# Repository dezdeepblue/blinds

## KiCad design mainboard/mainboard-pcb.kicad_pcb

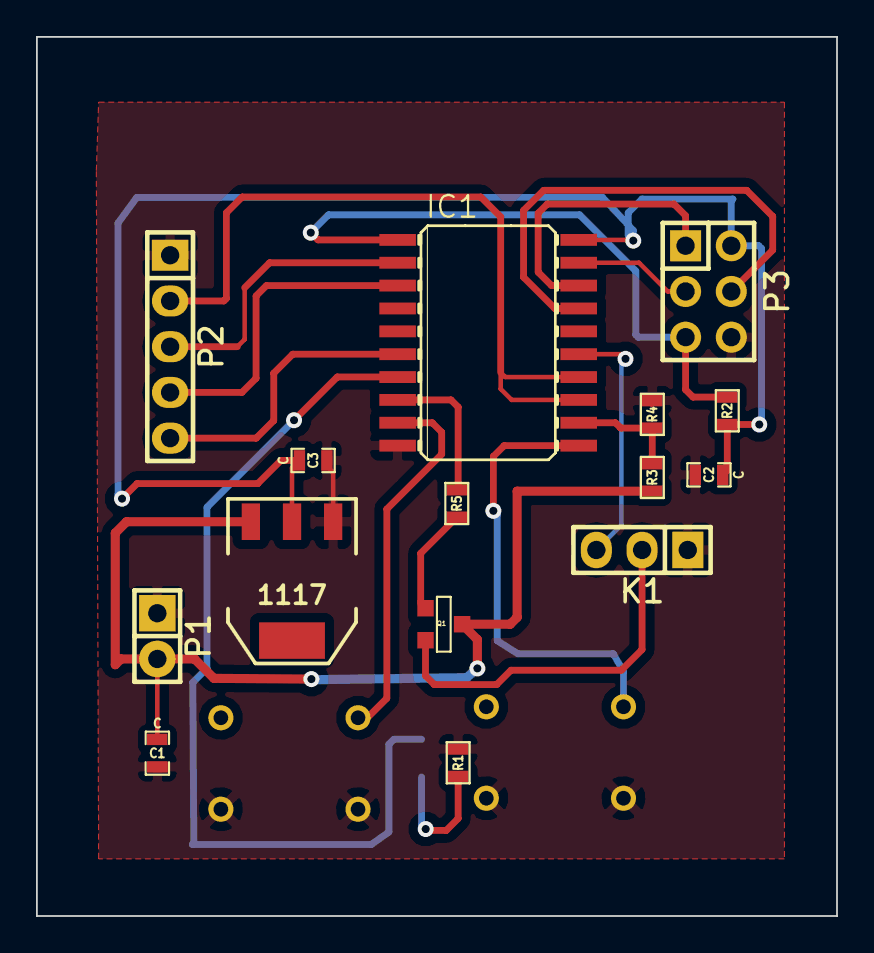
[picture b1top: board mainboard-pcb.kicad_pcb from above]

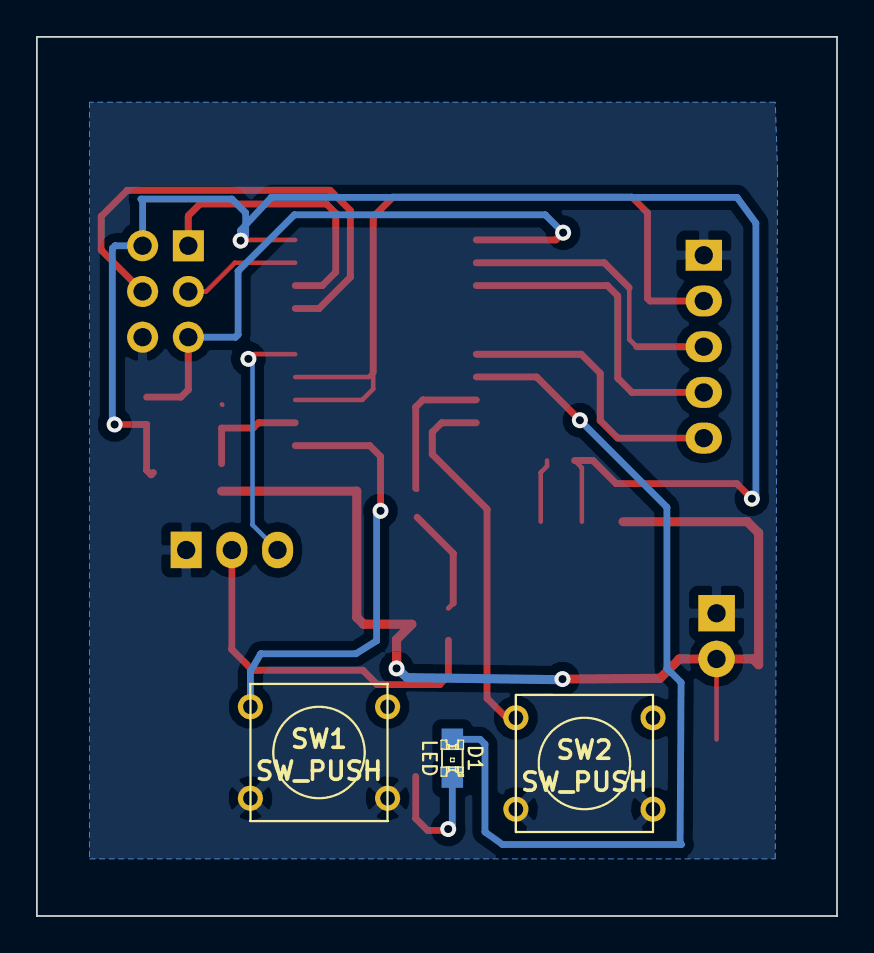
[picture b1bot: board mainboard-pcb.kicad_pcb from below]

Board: 2 copper layers, 44.4 x 48.8 mm, 18 parts (3 on the bottom side), 20 nets.

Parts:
1117: SOT223
C1, C2, C3: C; SM0603_Capa
D1: LED; LED-0805
IC1: ATTINY2313-S; SO20W
K1: CONN_3; Pin_Header_Straight_1x03
P1: CONN_2; Pin_Header_Straight_1x02
P2: CONN_5; Pin_Header_Straight_1x05
P3: CONN_3X2; Pin_Header_Straight_2x03
Q1: Q1; SOT23GDS
R1, R2, R3, R4, R5: R; SM0603
SW1, SW2: SW_PUSH; SW_PUSH_SMALL

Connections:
+BATT: 1117.3, C1.1, P1.2, Q1.D, R3.2
GND: 1117.1, C1.2, C2.2, C3.2, IC1.10, K1.1, P1.1, P2.1, P3.6, R1.2, R4.1, SW1.2, SW2.2
unnamed: 1117.2, C2.1, C3.1, IC1.20, P3.2, R2.1
unnamed: D1.1, IC1.7
unnamed: D1.2, R1.1
unnamed: IC1.1, P3.5, R2.2
unnamed: IC1.2, P2.3
unnamed: IC1.3, P2.4
unnamed: IC1.6, P2.5
unnamed: IC1.8, R5.2
unnamed: IC1.9, SW2.1
unnamed: IC1.11, SW1.1
unnamed: IC1.12, R3.1, R4.2
unnamed: IC1.13, IC1.14, P2.2
unnamed: IC1.15, K1.3
unnamed: IC1.17, P3.4
unnamed: IC1.18, P3.1
unnamed: IC1.19, P3.3
unnamed: K1.2, Q1.S
unnamed: Q1.G, R5.1

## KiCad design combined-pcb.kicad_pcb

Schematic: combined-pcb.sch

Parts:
C1, C2: C; dp_devices-C0.1PTH
J1: CON_HEADER_1X02-PTH; dp_devices-M1X2
J2: CON_HEADER_1X03-PTH; dp_devices-M1X3
Q1, Q2: TRANSISTOR_NPNTO92; SparkFun-TO-92
R1, R2: RESISTOR1206; SparkFun-1206
U1: ARDUINO_MINI
U2: NCP1117ST33T3G
U3: BLUETOOTH-HC05

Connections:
/GND: C1.2, C2.2, J1.1, Q1.1 (E), U1.23 (GND2), U2.1 (GND), U3.13 (GND)
unnamed: C1.1, J1.2, J2.2, U2.3 (VI)
unnamed: C2.1, U1.21 (VCC), U2.2 (VO)
unnamed: J2.1, Q1.3 (C)
unnamed: J2.3, R2.2
unnamed: Q1.2 (B), R1.2
unnamed: R1.1, U1.15 (12)
unnamed: R2.1, U1.13 (10)
unnamed: U1.1 (TX0), U3.2 (UART_RXD)
unnamed: U1.2 (RX1), U3.1 (UART_TXD)
unnamed: U1.8 (5), U3.12 (VCC)

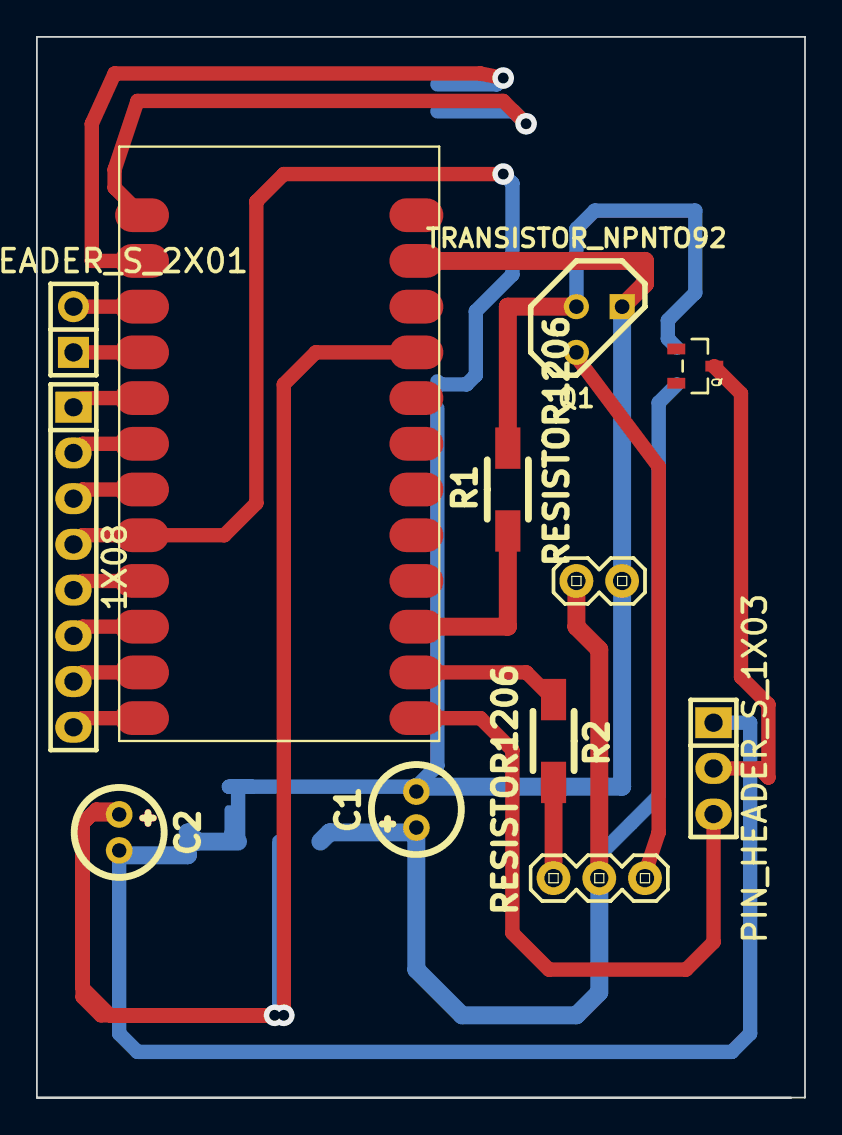
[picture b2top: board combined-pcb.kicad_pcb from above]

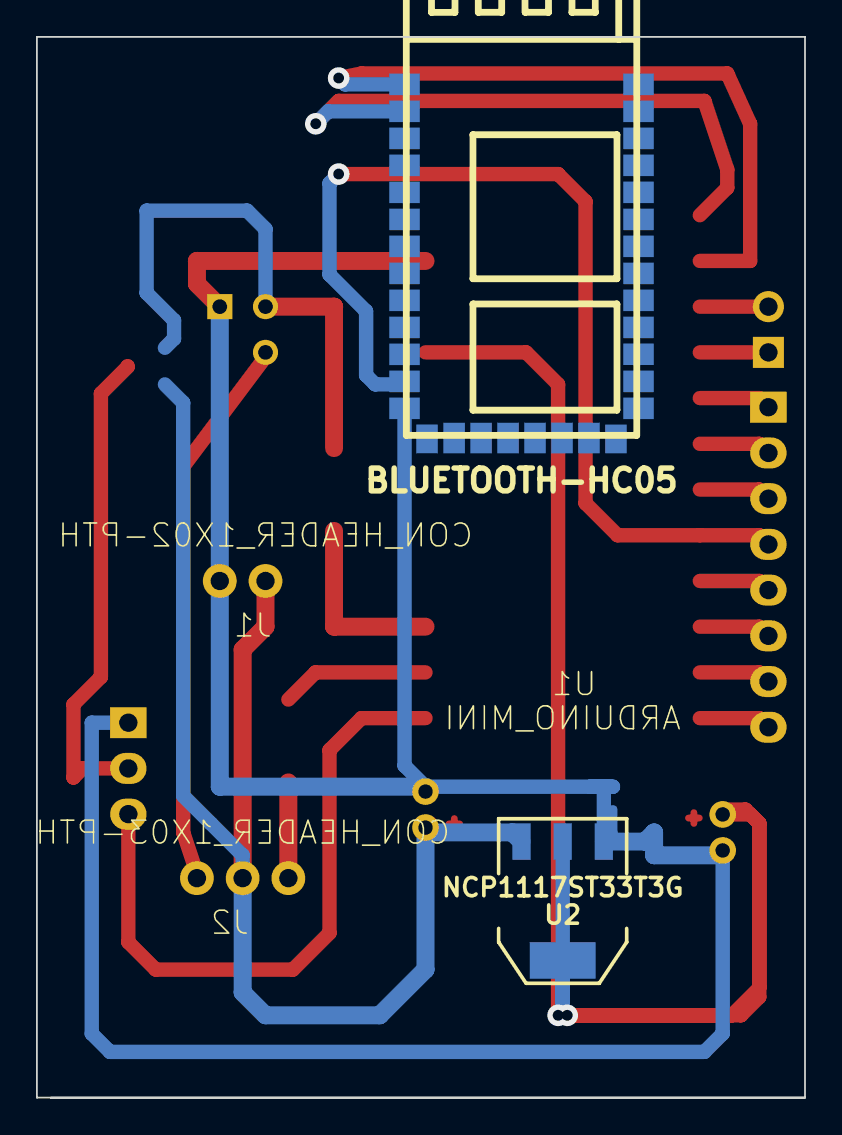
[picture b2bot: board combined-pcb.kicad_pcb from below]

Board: 2 copper layers, 42.7 x 58.9 mm, 14 parts (2 on the bottom side), 11 nets.

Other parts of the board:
1X08: Val**; Pin_Header_Straight_1x08
PIN_HEADER_S_1X03: Val**; Pin_Header_Straight_1x03
PIN_HEADER_S_2X01: Val**; Pin_Header_Straight_2x01
Q: SOT23; sot23

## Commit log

2014-07-02 added bunch
2014-07-03 started some coding
2014-07-09 scad files done
2014-07-09 added in both pcs
2014-07-09 added filament compensation to frame-base and wall-server components
2014-07-09 added more compenstaion variables
2014-07-10 scad changest to almost all files ready for reprint
2014-07-13 changed wall width to 42 - changed style to plugin for fan adapter changed width of frame base to 26 changed adapters - now there are fan adapters on both side
2014-07-13 minor changes to rounded corners
2014-07-14 cad files edit'ed again for sizing/change slot1 fitting.
2014-07-15 changed to references file
2014-07-15 added inventor ref file and created front wall in inventor
2014-07-16 some inventor junk
2014-07-17 all autodesk walls done and cover
2014-07-18 added servo part
2014-07-19 added a file for sunil
2014-07-21 minor changes
2014-07-21 breakout inventor files
2014-07-21 Created inventor dir and stls
2014-07-22 inventor stls - make arm fit within walls
2014-07-25 added channel to the arm-slot and end-wall for adapters
2014-07-26 added kicad files
2014-07-27 kicad file done
2014-07-29 added sunil stuff and playing around with eagle etc
